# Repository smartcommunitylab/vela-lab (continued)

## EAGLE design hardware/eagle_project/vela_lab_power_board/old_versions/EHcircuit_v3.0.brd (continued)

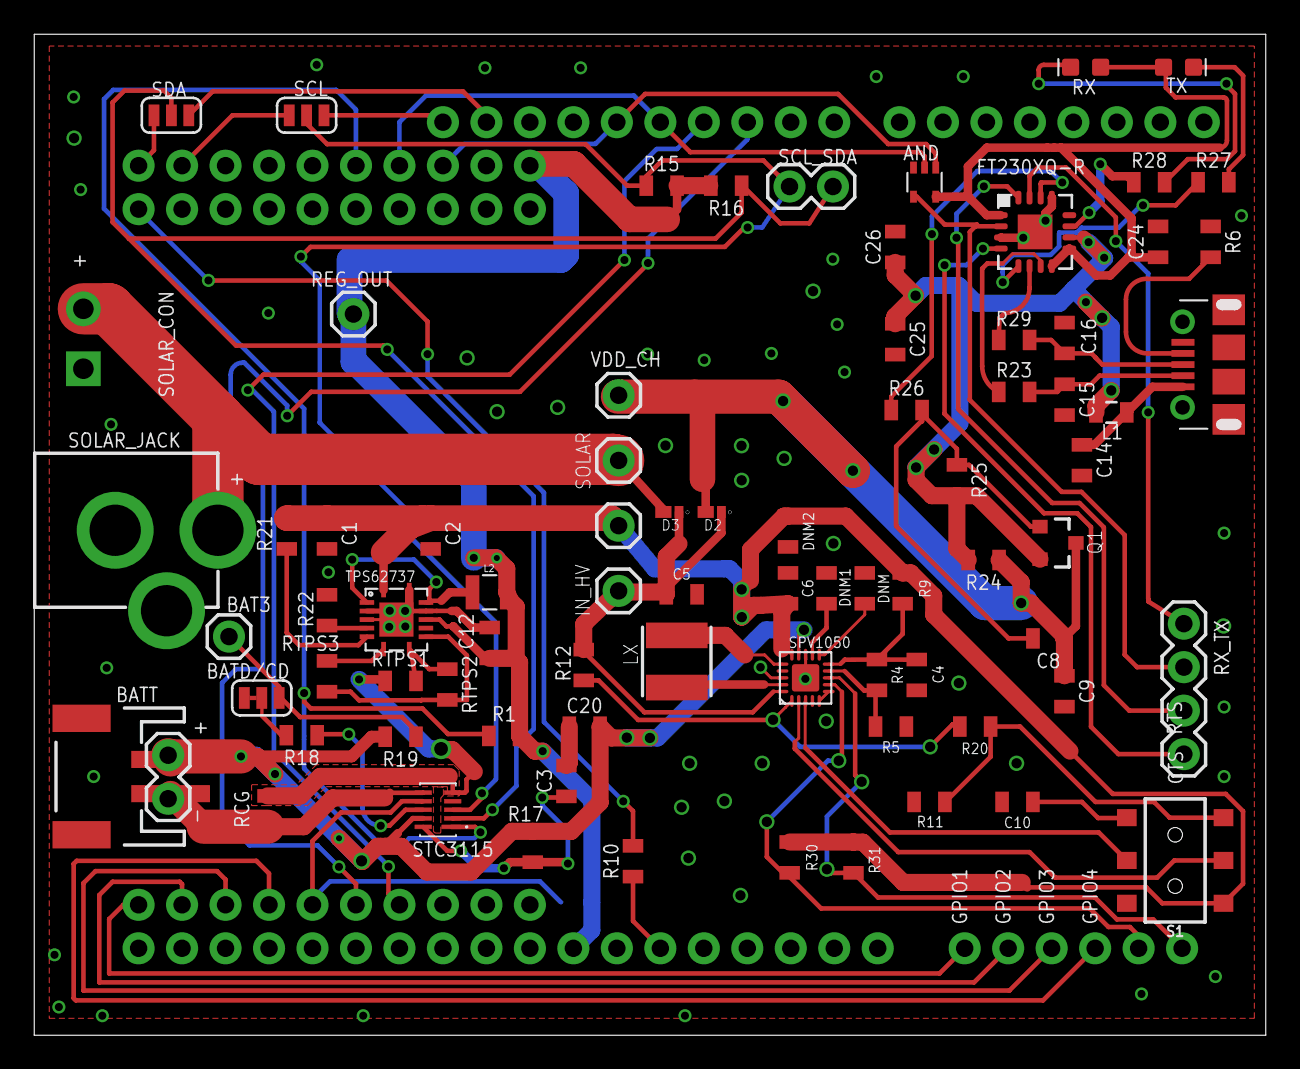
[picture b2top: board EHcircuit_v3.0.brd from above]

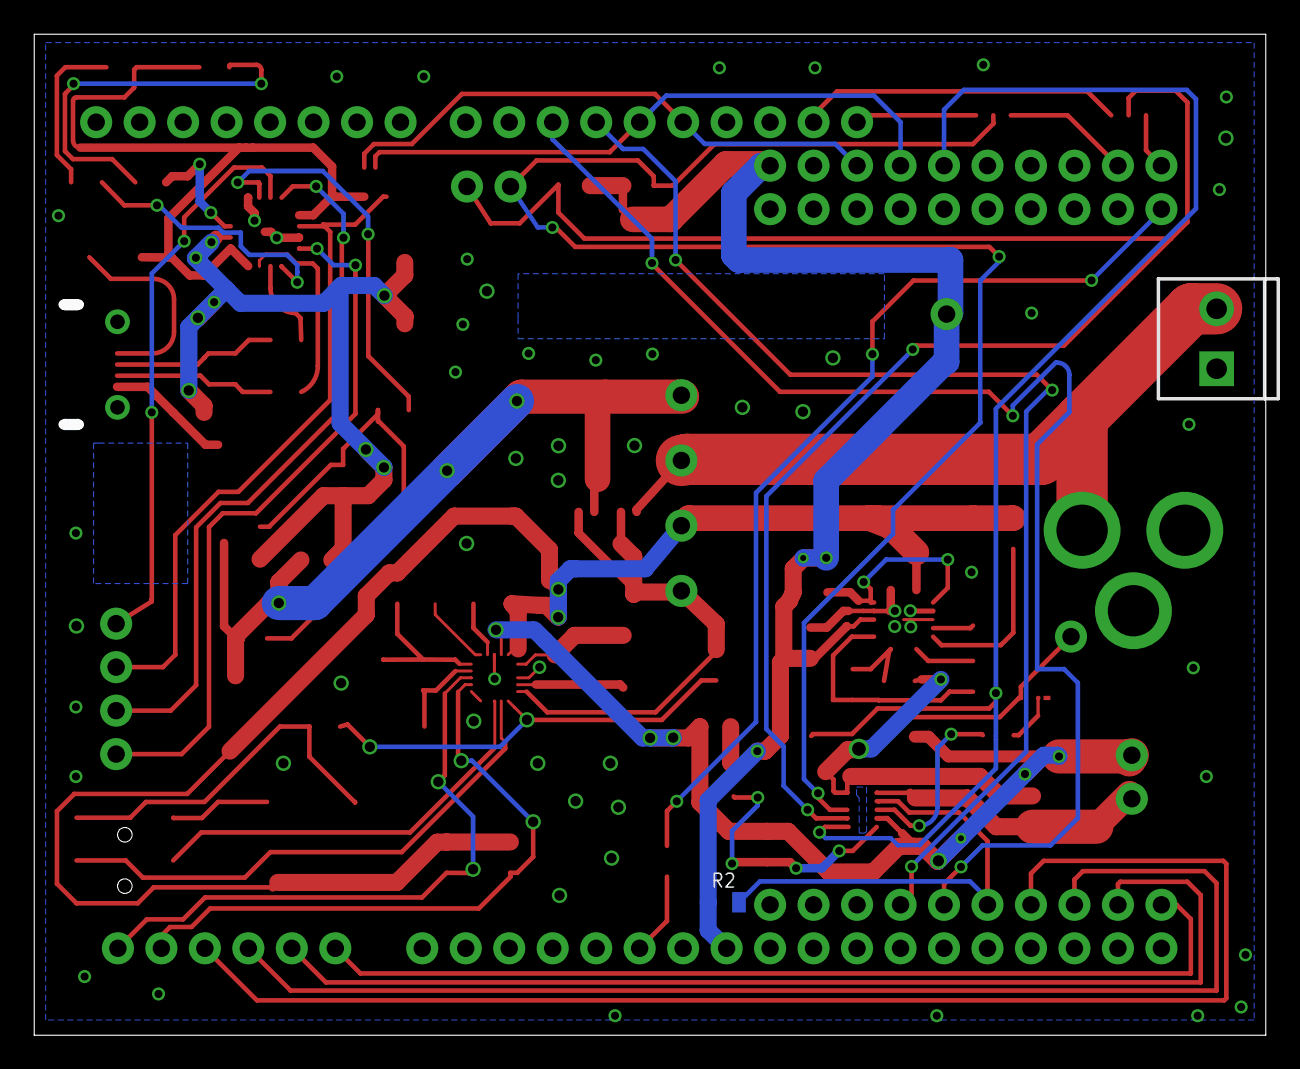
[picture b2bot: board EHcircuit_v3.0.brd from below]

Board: 2 copper layers, 71.9 x 58.5 mm, 82 parts (2 on the bottom side), 67 nets.

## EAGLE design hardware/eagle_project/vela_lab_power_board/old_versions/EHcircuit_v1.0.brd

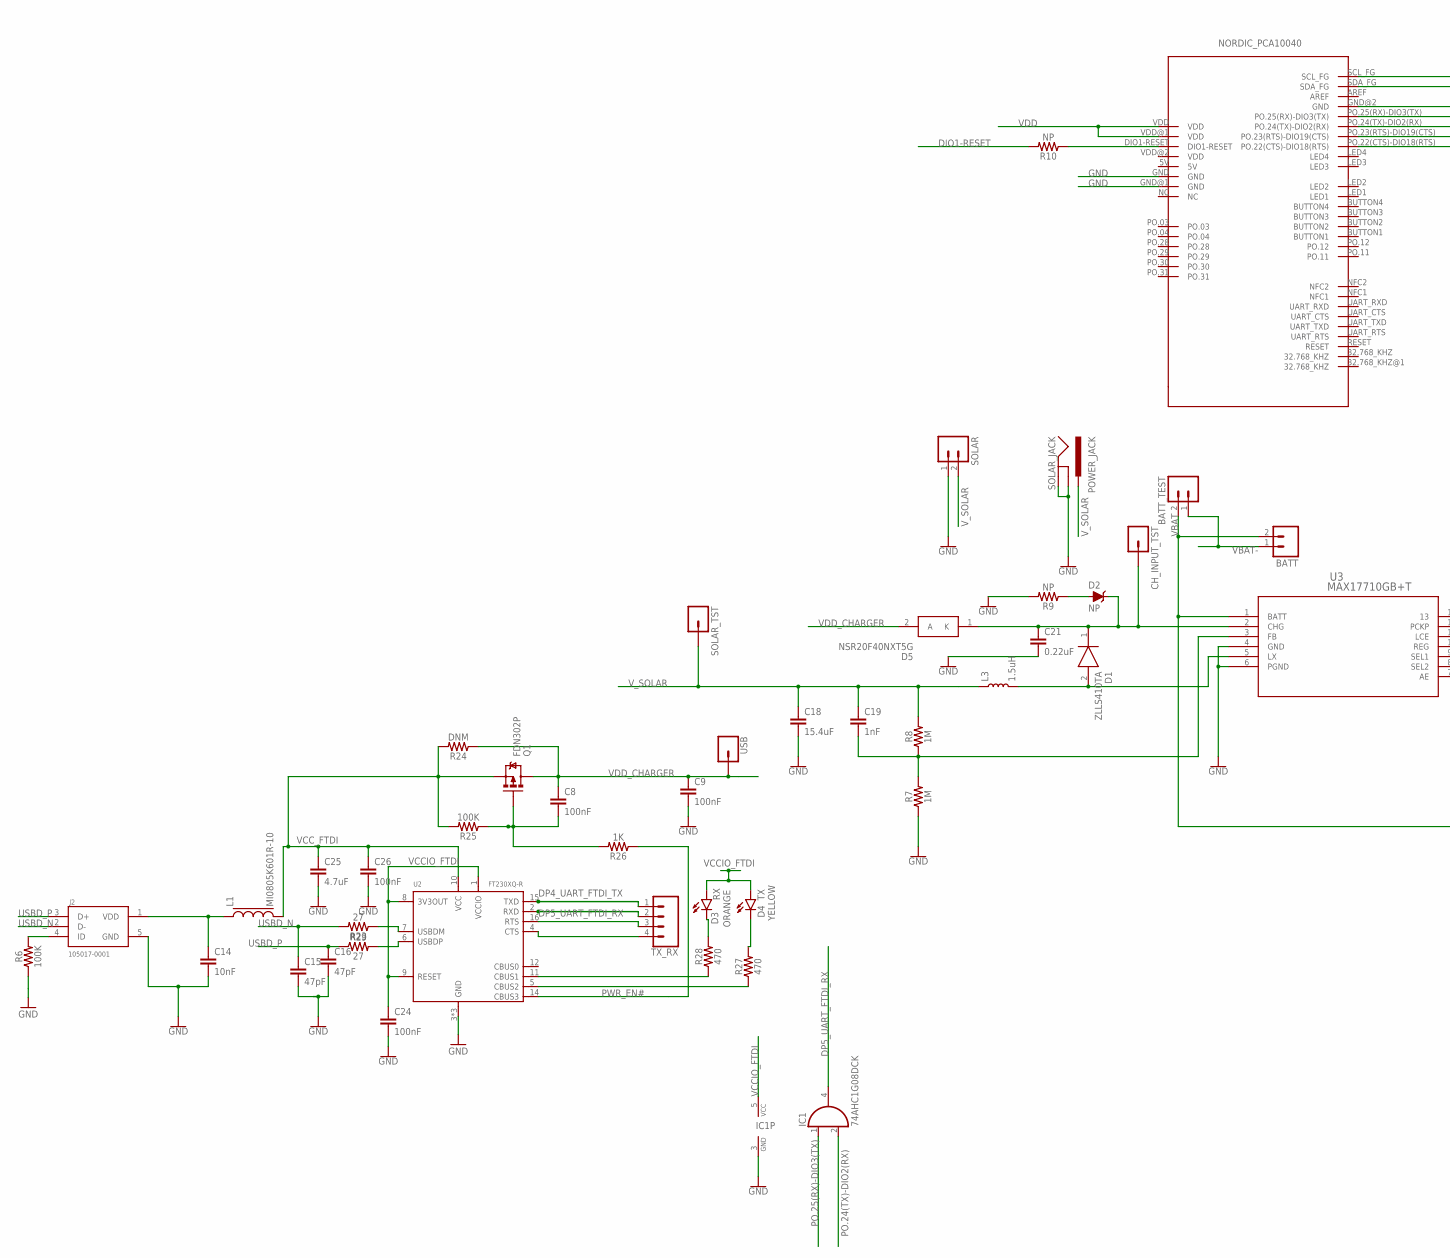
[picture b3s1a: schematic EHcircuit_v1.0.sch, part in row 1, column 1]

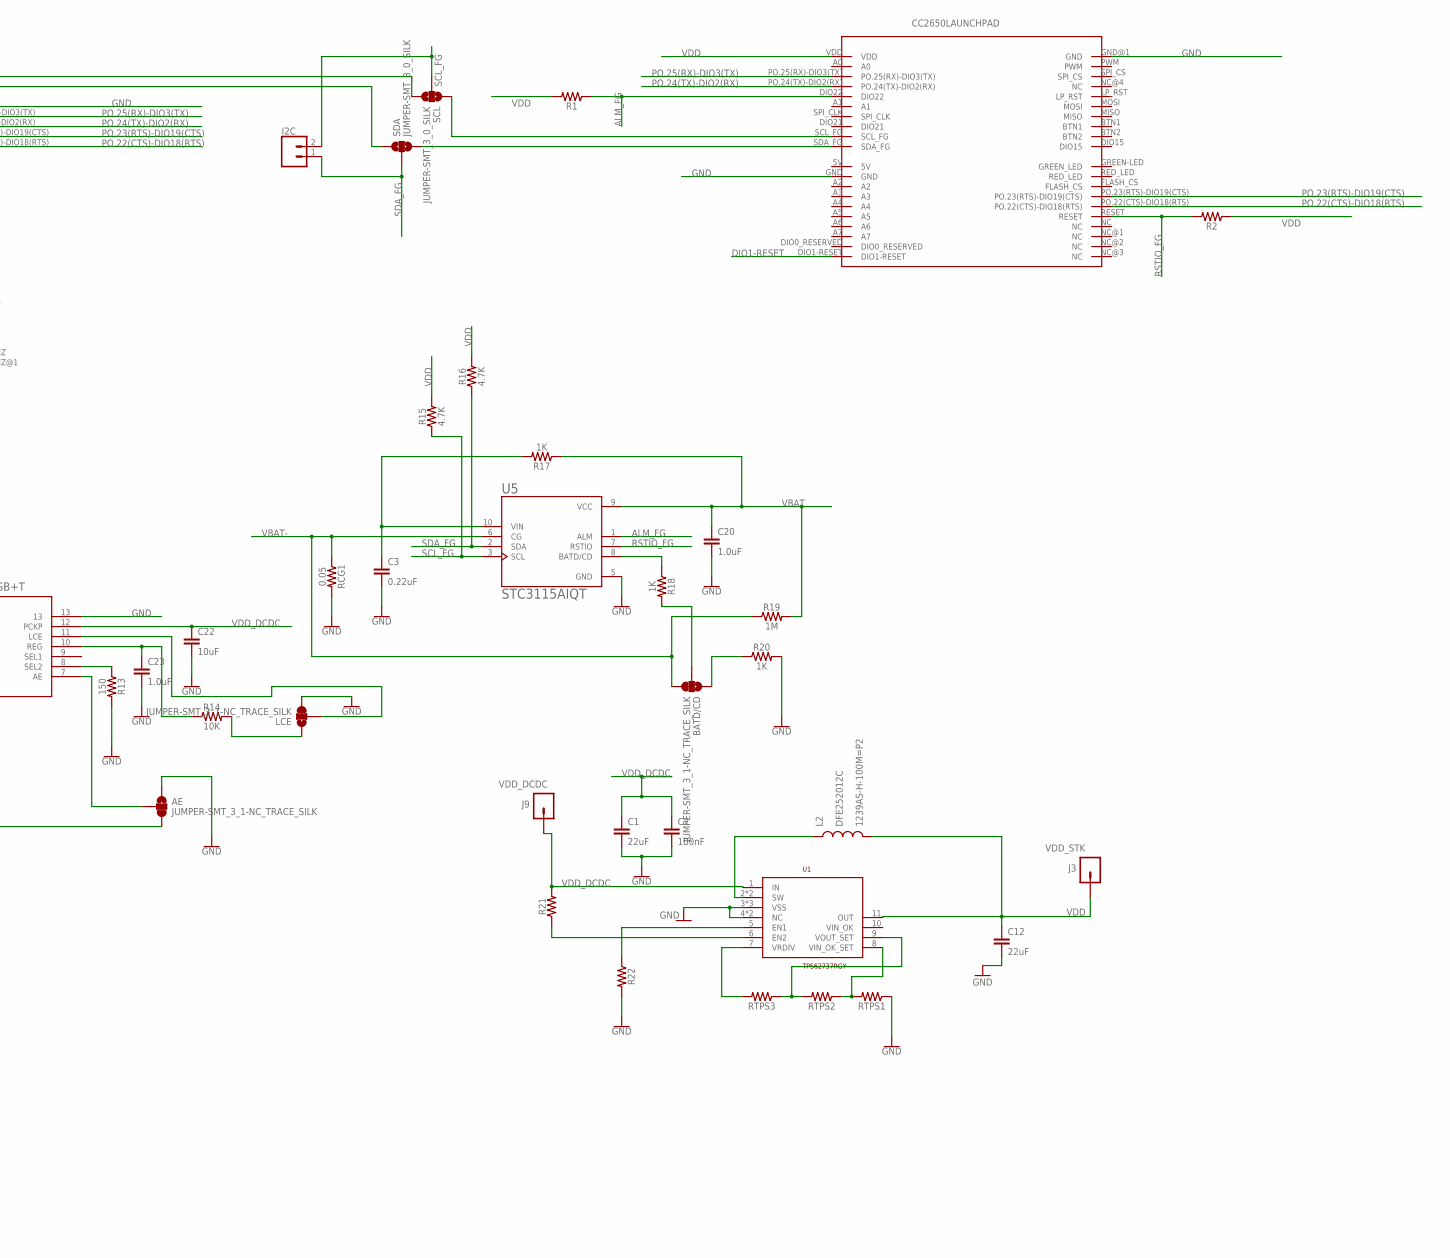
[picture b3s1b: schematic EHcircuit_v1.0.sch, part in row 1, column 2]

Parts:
AE: JUMPER-SMT_3_1-NC_TRACE_SILK; SMT-JUMPER_3_1-NC_TRACE_SILK
BATD/CD: JUMPER-SMT_3_1-NC_TRACE_SILK; SMT-JUMPER_3_1-NC_TRACE_SILK
BATT: M02-JST-2MM-SMT; JST-2-SMD@1
BATT_TEST: M02PTH; 1X02@1
C1, C12: 22uF; 0805
C2, C8, C9, C24, C26: 100nF; 0805
C3, C21: 0.22uF; 0805
C14: 10nF; 0805
C15, C16: 47pF; 0805
C18: 15.4uF; 0805
C19: 1nF; 0805
C20, C23: 1.0uF; 0805
C22: 10uF; 0805
C25: 4.7uF; 0805
CH_INPUT_TST: M01PTH; 1X01@1
D1: ZLLS410TA; SOD2513X120N
D2: NP; SOD-323@1
D3: ORANGE; LED-0603
D4: YELLOW; LED-0603
D5: NSR20F40NXT5G; DSN2_1
I2C: CONN_02; 1X02
IC1: 74AHC1G08DCK; SC70-5
J2: 105017-0001; MOLEX_105017-0001
J3, J9: M01PTH; 1X01@1
L1: MI0805K601R-10; 0805
L2: 1239AS-H-100M=P2; DFE252012C
L3: 1.5uH; XFL4020
LCE: JUMPER-SMT_3_1-NC_TRACE_SILK; SMT-JUMPER_3_1-NC_TRACE_SILK
Q1: FDN302P; SOT23-3
R1, R2, R21, R22: 0.3OHM-0805-1/8W-1%; 0805
R6, R25: 100K; 0805
R7, R8, R19: 1M; 0805
R9, R10: NP; 0805
R13: 150; 0805
R14: 10K; 0805
R15, R16: 4.7K; 0805
R17, R18, R20, R26: 1K; 0805
R23, R29: 27; 0805
R24: DNM; 0805
R27, R28: 470; 0805
RB2: CC2650LAUNCHPAD; SEPS_RB
RCG1: 0.05; 0805
RTPS1, RTPS2, RTPS3: 0.3OHM-0805-1/8W-1%; 0805
SCL: JUMPER-SMT_3_0_SILK; SMT-JUMPER_3_0_NC_TRACE_SILK
SDA: JUMPER-SMT_3_0_SILK; SMT-JUMPER_3_0_NC_TRACE_SILK
SOLAR: M023.5MM; SCREWTERMINAL-3.5MM-2@1
SOLAR_JACK: POWER_JACK; POWER_JACK_PTH
SOLAR_TST: M01PTH; 1X01@1
TX_RX: CONN_04; 1X04
U1: TPS62737RGY; QFN14
U2: FT230XQ-R; QFN16
U3: MAX17710GB+T; 21-0451C
U5: STC3115AIQT; SON50P200X300X60-10
U$1: PCA10040NORDIC; SEPS_BB
USB: CONN_01; 1X01

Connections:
ALM_FG: R1.1, RB2.DIO22, U5.1 (ALM)
DIO1-RESET: R10.2, RB2.DIO1-RESET
DP4_UART_FTDI_TX: TX_RX.1, U2.15 (TXD)
DP5_UART_FTDI_RX: IC1.4 (O), TX_RX.2, U2.2 (RXD)
GND: AE.1, C1.2, C2.2, C3.2, C9.2, C12.2, C14.2, C15.2, C16.2, C18.2, C20.2, C21.2, C22.2, C23.2, C24.2, C25.2, C26.2, IC1.3 (GND), J2.5 (GND), LCE.3, R6.1, R7.1, R9.2, R13.2, R20.2, R22.2, RB2.GND, RB2.GND@1 (GND), RCG1.2, RTPS1.1, SOLAR.1, SOLAR_JACK.GND, SOLAR_JACK.GNDBREAK, U1.3 (VSS), U1.4 (NC), U1.12 (VSS), U1.14 (NC), U1.TH_PAD (VSS), U2.3 (GND), U2.13 (GND), U2.17 (GND), U3.4 (GND), U3.6 (PGND), U3.13, U5.5 (GND), U$1.GND, U$1.GND@1 (GND), U$1.GND@2 (GND)
unnamed: R28.1, U2.11 (CBUS1)
unnamed: C14.1, J2.1 (VDD), L1.1
unnamed: C8.2, Q1.1 (G), R25.1, R26.2
unnamed: RTPS1.2, RTPS2.1, U1.8 (VIN_OK_SET)
unnamed: R18.1, U5.8 (BATD/CD)
unnamed: R22.1, U1.5 (EN1)
unnamed: D1.2 (A), L3.P$2 (2), U3.5 (LX)
unnamed: D2.A, R9.1
unnamed: C19.2, R7.2, R8.1, U3.3 (FB)
unnamed: R21.1, U1.6 (EN2)
unnamed: L2.P$1 (1), U1.2 (SW), U1.13 (SW)
unnamed: RB2.SCL_FG, SCL.1
unnamed: C23.1, R14.1, U3.10 (REG)
unnamed: R27.1, U2.5 (CBUS2)
unnamed: LCE.2, U3.11 (LCE)
unnamed: R13.1, U3.8 (SEL2)
unnamed: LCE.1, R14.2
unnamed: J2.4 (ID), R6.2
unnamed: AE.2, U3.7 (AE)
unnamed: D3.C, R28.2
unnamed: R10.1, U$1.DIO1-RESET
unnamed: RTPS3.2, U1.7 (VRDIV)
unnamed: RB2.SDA_FG, SDA.3
unnamed: D4.C, R27.2
unnamed: BATD/CD.2, R18.2
unnamed: RTPS2.2, RTPS3.1, U1.9 (VOUT_SET)
unnamed: SDA.1, U$1.SDA_FG
unnamed: SCL.3, U$1.SCL_FG
unnamed: BATD/CD.1, R20.1
unnamed: C21.1, CH_INPUT_TST.1, D1.1 (K), D2.C, D5.1 (K), U3.2 (CHG)
unnamed: R23.1, U2.7 (USBDM)
unnamed: R29.2, U2.6 (USBDP)
unnamed: TX_RX.3, U2.16 (RTS)
unnamed: C3.1, R17.2, U5.10 (VIN)
unnamed: TX_RX.4, U2.4 (CTS)
PO.22(CTS)-DIO18(RTS): RB2.PO.22(CTS)-DIO18(RT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, U$1.PO.22(CTS)-DIO18(RT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
PO.23(RTS)-DIO19(CTS): RB2.PO.23(RTS)-DIO19(CT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, U$1.PO.23(RTS)-DIO19(CT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
PO.24(TX)-DIO2(RX): IC1.2 (I1), RB2.PO.24(TX)-DIO2(RX), U$1.PO.24(TX)-DIO2(RX)
PO.25(RX)-DIO3(TX): IC1.1 (I0), RB2.PO.25(RX)-DIO3(TX), U$1.PO.25(RX)-DIO3(TX)
PWR_EN#: R26.1, U2.14 (CBUS3)
RSTIO_FG: R2.2, RB2.RESET, U5.7 (RSTIO)
SCL_FG: I2C.2, R15.1, SCL.2, U5.3 (SCL)
SDA_FG: I2C.1, R16.1, SDA.2, U5.2 (SDA)
USBD_N: C15.1, J2.2 (D-), R23.2
USBD_P: C16.1, J2.3 (D+), R29.1
VBAT: AE.3, BATT.2 (1), BATT_TEST.2, C20.1, R17.1, R19.2, U3.1 (BATT), U5.9 (VCC)
VBAT-: BATD/CD.3, BATT.1 (2), BATT_TEST.1, R19.1, RCG1.1, U5.6 (CG)
VCCIO_FTDI: C24.1, D3.A, D4.A, IC1.5 (VCC), U2.1 (VCCIO), U2.8 (3V3OUT), U2.9 (RESET)
VCC_FTDI: C25.1, C26.1, L1.2, Q1.2 (S), R24.2, R25.2, U2.10 (VCC)
VDD: C12.1, J3.1, L2.P$2 (2), R1.2, R2.1, R15.2, R16.2, RB2.VDD, U1.11 (OUT), U$1.VDD, U$1.VDD@1 (VDD)
VDD_CHARGER: C8.1, C9.1, D5.2 (A), Q1.3 (D), R24.1, USB.1
VDD_DCDC: C1.1, C2.1, C22.1, J9.1, R21.2, U1.1 (IN), U3.12 (PCKP)
V_SOLAR: C18.1, C19.1, L3.P$1 (1), R8.2, SOLAR.2, SOLAR_JACK.PWR, SOLAR_TST.1

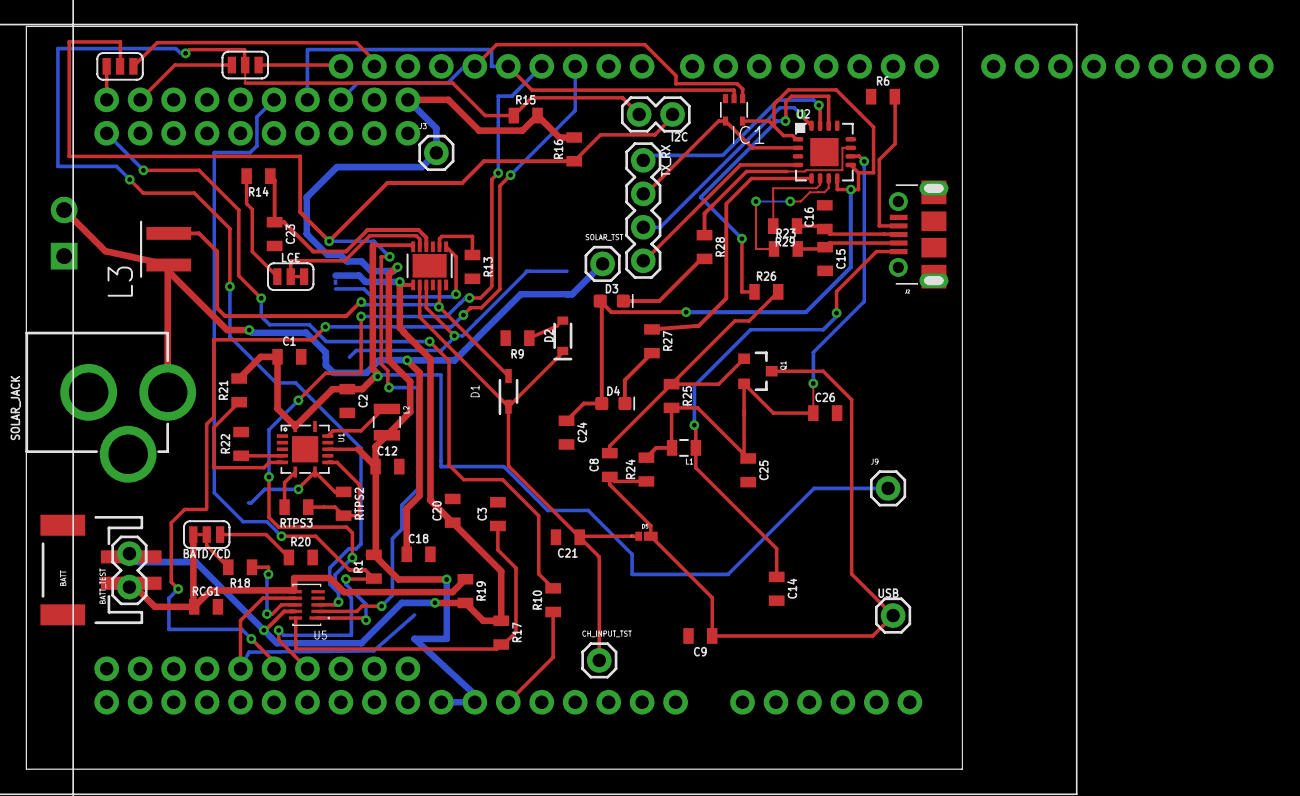
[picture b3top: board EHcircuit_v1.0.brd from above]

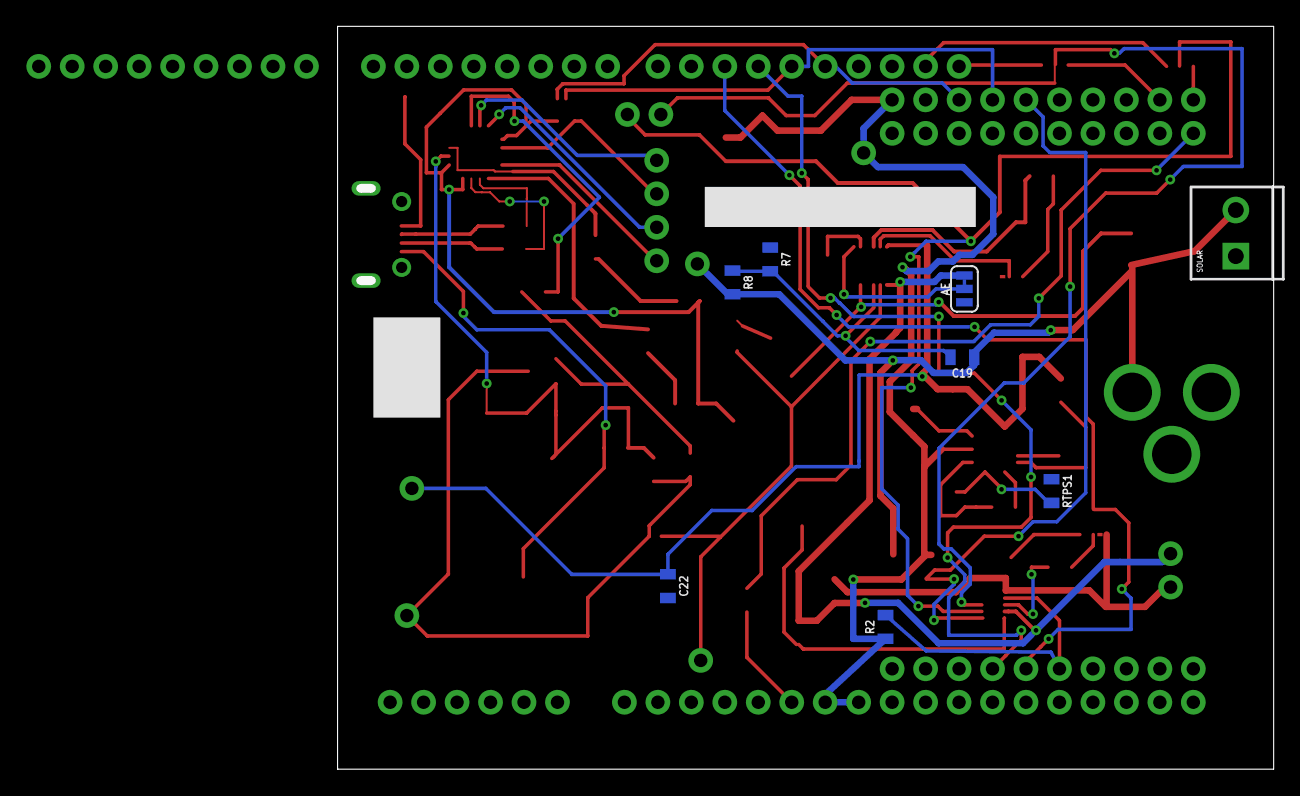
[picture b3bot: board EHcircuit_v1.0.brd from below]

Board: 2 copper layers, 71.0 x 56.4 mm, 79 parts (8 on the bottom side), 58 nets.

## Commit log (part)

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2017-11-15 First commit
    First version of the code (anyway it compiles and works).
    This commit is only for backup purposes
2017-11-17 Various improvements on UART communication and BLE scanning
    - uart ack change to application ack
    - add uart_resp_bt_neigh_rep_end type to indicate the report is over
    - ack error now have one argument with some data regarding the ack
    - added contraints.h which contains various constants used by the projects
    - added filter for BLE beacons (filters CLIMBC nodes and eddystone with the correct namespace)
    - Makefile clean
2017-11-17 Changing report
    - now the "seen_since" field of the report is in second (16 bits), no more in millis
    - the report includes also the beacon_msg_count
2017-11-21 Blink led on nrf52dk and code version on both boards
    - an uart ack error is signaled with a blink of led4 in the nrf52dk
    - the code version string is added as payload of the uart_ready messagges. The build number is automatically increased by the build_script.sh. Thi
2017-11-21 Minor changes on app_timer (nrf52dk)
2017-11-21 Use struct in place of ptr+size
    moving data_t into uart_util.h so that now it is shared
2017-11-21 integration code --- currently not working
2017-11-21 Moving the uart flow control enable outside contiki sources
    By default contiki do not enable flow control on the uart but we need it.
    Now the enable is done in uart_util.c when the initialization routine is called.
2017-11-22 Updated to match the new structure of the test directories
2017-11-22 bringing makefile in line with new unit test structure for uart
2017-11-22 moving the shared struct definition of the buffer to common/inc/constraints.h
2017-11-22 Remove test-uart.c
    the file content has been moved to vela_uart.c
2017-11-22 working version of the dummy uart with the real RPL sender and receiver.
2017-11-22 fixing repository to add missing files for test sender
2017-11-22 Bug fix
    There was a logic error when the report was splitted in multiple uart packets.
2017-11-22 Bug fix for reports on splitted uart packets
2017-11-22 Adding simple readme to "integrate_sender_uart"
2017-11-23 Bojan: git setup test
2017-11-23 fixing debug to off
2017-11-23 Bojan: excluded aux files for linux folder
2017-11-23 Version 0.1
    Not stable but seems to work
2017-11-28 BM: added gateway subdir and code
2017-11-28 BM: doc update
2017-11-28 decreasing uart baudrate
    working at 1M give errors, then switch to 115200
2017-11-29 BM: corrected typo in /gateway/dev/serial_test/
2017-11-30 Reduce BT scan duty cycle
2017-11-30 BM: serial testing
2017-11-30 Minor optimization/fix
2017-11-30 BM: serial for real packets (not decoded)
2017-12-01 BM: added serial test log and gitignore
2017-12-01 BM: serial test log update
2017-12-04 uart_util optimization/fix
    This fix lightly reinforce the uart communication
2017-12-04 channel check rate change
2017-12-05 uart tx_error led fix
    the tx_error led weren't reset properly
2017-12-05 BM: gateway integration dev
2017-12-06 remove printf during
2017-12-07 BM: packet read lenght check
2017-12-12 BM: added app log
2017-12-13 BM: packet reception testing
2017-12-15 Reorganization of defines in the header files
    The rpl packet size has been increased from 10 to 15 contacts
2017-12-15 BM: added matlab folder and scripts
2017-12-20 BM: added demo script
2018-01-25 Comments change
    Just adding comments and removing some useless stuf
2018-10-02 New design added
2018-10-05 Small fixes pcb design
2018-10-05 First check. Few things to modify:
    - rearrange kelvin connections on sensing resistor (and routing around the fuel gauge)
    - add LED on CBUS1 and CBUS2 of the FTDI chip (see powerDevPack project), or remove the CBUS1 and CBUS2 connections
    - edit the JST connector footprint and increase holes size (see J5 footprint as reference)
2018-10-08 Changed drill holes in JST connectors
2018-10-08 Updated .gitignore file
2018-10-08 Changed sense resistor
2018-11-12 commiting the PCB printed ad eurocircuit (very first version)
2018-11-26 Add UART interupt priority on VELA NODES
2018-11-26 Fix CCS project
2018-11-26 add workaround the TX/RX swap in the solar panel board
2018-11-26 minor fix to a makefile
2018-11-27 Small change in the uart_util.c
    There was a risk of entering infinite loop if the status = error
2018-11-28 putchar fix
2018-11-28 All makefile are now similar
2018-11-29 PCB project update
    - arduino header fix
    - text fix
    - library refactor (now all the capacitor use the same component as well as resistors)
2018-12-05 Adding MAX17260 temperature reading
2018-12-06 Updated network messages types
2018-12-06 getting rid of the fsm. Now vela_uart uses procedures to execute queue of commands
2018-12-07 add uart_util_is_waiting_ack to uart_util
2018-12-07 Code used for test with fuel gauge and gateway commands
2018-12-12 Sequential procedures module
    - now to communicate over the uart both boards use sequential_procedure module
    - added log over rtt on the nordic
    - added verbosity on both boards
2018-12-12 Stable version?
2018-12-13 gitignore
2018-12-13 trickle fix (multihop was not working)
2018-12-14 commented part forgotten
2018-12-19 Changed raw data logging formatting
2018-12-19 Adding delay to ack.
    It seemed that the TI sent the uart ack to fast and the nordic wasn't able to handle it
2018-12-19 message number fix
2018-12-20 Changed raw data logging for bluetooth reports
2018-12-20 Clean up gateway code
2018-12-21 Add a delay on ack also on nordic and on sequential procedures
2019-01-02 increasing ser usability.
    Now, on the gateway script, if the serial line has an exception the script keep checking every 5s and if it returns available the script restart working
2019-01-03 minor change: activating bluetooth scheduling (30 min on/30 min off)
2019-01-04 minor PRINTF change
2019-01-04 fix on report timeout.
    Now it properly stores the last value and use it till a new timeout is received from the mesh network
2019-01-04 Minor parameters change
2019-01-07 Fixed contact data plotter
2019-01-10 Increased max packet size
2019-01-14 Updated network_commands document
2019-01-15 Restructuring and changing documentation
2019-01-15 Edited README.md
2019-01-28 minor bug (if nordic was reset and the report was enabled a reset was triggered)
2019-01-29 regardless where the script is launched, logs are always in the same position of the script
2019-01-29 Merge branch 'master' of https://github.com/smartcommunitylab/vela-lab
    # Please enter a commit message to explain why this merge is necessary,
    # especially if it merges an updated upstream into a topic branch.
    #
    # Lines starting with '#' will be ignored, and an empty message aborts
    # the commit.
2019-01-29 remove self reset with NORDIC_WATCHDOG_ENABLED
2019-01-30 allow events on ti even if ready message from nordic isn't received
    this otherwise the nordic cannot be recovered after a bad boot
2019-01-31 redesign of the terminal interface
2019-02-01 minor graphical stuff on python script
2019-02-05 bug fix
2019-02-18 add 'forced' option to trickle messages
2019-02-18 Better handling of unknwown uart part
2019-02-19 a random delay is added to the handling of all the trickle packets. This to avoid collisions
2019-02-21 Some graphical fix and improvement and general log revision
2019-03-06 adding command line argument to set the port
2019-03-13 adding a kind of lock to avoid command handling during the transmission of the BLE report from the nordic to the TI, also a better handling of uart_util_ack_error
2019-03-13 minor makefile change
2019-05-15 Code cleanup - especially for send messages - ALM increased network message size to 22 entries - ALM
2019-05-15 gitignore + build.sh
2019-07-04 adding basic sender that works in cooja
2019-07-04 fixed type-o
2019-08-08 first commit with OTA. There are still things to fix, with all the code, the OTA cannot be verified because of memory overflow and the node reboots.
2019-08-12 fix in doc
2019-08-12 more reliable ota
2019-08-16 better ota
    If the node doesn't have enough free ram to store the CRC result in the ext-flash, it will be the bootloader to do it on the next reboot.
2019-08-20 bug fix in OTA that locked the bootloader in an infinite loop in case of crc error
2019-08-22 added the payload checksum in the gateway to sink communication
2019-08-26 Checksum fix on sink
2019-08-30 gitignore and some experiment log
2019-09-02 Various proximity detection algorithm improvements
2019-09-03 stronger algorithm and octave for raspberry (installed with flatpak)
2019-10-08 code clean e better gui (with fw info embedded)
2019-10-09 some cleaning and network status generation for mqtt push
2019-10-11 stability updates
2019-10-11 Main readme and other doc update
2019-10-11 remove bin
2019-10-14 Readme
2019-10-14 VSCode+GDB+openOCD working
    Some configuration such as those involving the bootloader are still not working.
    Removed all the references to eclipse and derivatives
2019-10-17 add mqtt connection to thingsboard
2019-10-17 change the format of events generated by the octave script
    Now the format is ready to be pushed on a gateway device of thingsboard
2019-10-18 Environment fix
    - files are no more copied to integrate_sender_uart
    - files such as vela_uart.c/.h vela_sender.c/h and others are now packed as contiki modules
    - some contiki test projects (no more used) have been moved to old/ directory
    - improved clean.sh
    - improved build scripts
    - added the VSCode tasks to compile for OTA download
2019-10-24 mqtt connection check + other minor changes
2019-10-24 sink baudrate to 1M (second)
2019-10-29 relative path for startup script
2019-10-29 re-enable logs, without logs the sink reboots during ota
2019-10-30 minor things
2019-11-20 change in the message format transmitted to thingsboard
2019-11-20 add the vscode launch configuration for the gateway
2019-11-22 get beacon improvement
    - now it loops over all the nodes (node list is hardcoded)
2019-12-04 moving contiki to gitlab and embedding NRF SDK in the repo through a submodule
    Moreover few README change
2019-12-04 readme update
2019-12-04 readme format
2019-12-04 readme update n
2019-12-04 change to README-BUILDING
2019-12-04 typos in readmes
2019-12-18 my last commit with residual changes
    - bug fix on main.py
    - workspace with relative paths
    - bug fix in backend scripts
    - minor improvements here and there
2020-11-12 added version file to gitignore
2020-11-12 added vela_node_with_bootloader to gitignore
2020-11-16 shifted main inside if __main__ and added another token
2020-11-16 starting to collect packages in requirements
2020-11-18 porting the variables to different files
2020-11-19 unique file containing the parameters
2020-11-20 modification to the proximity detection trhough octave
2020-11-20 added comment
2020-11-20 moved the on_events because not related with the class itself
2020-11-25 log folder issue
2020-11-27 moved bluetooth parameters, but the command 5 still doesn't work
2020-12-01 added threading and firmware variables, some counter for callback debugging
2020-12-10 bluetooth scheduler, still too many beacon generates problems
2020-12-14 decode payload modified input parameters
2020-12-15 added possibility to disable bluetooth scheduler and proximity detection script
2021-01-19 added file for beacon processing
2021-02-22 changed sleep function, removed useless initialization in processo uart rx function
2021-02-22 modification about TOF and GATT
2021-03-29 backup for app_uart library, even if not working in vela-system
2021-04-20 nb_report_util added
2021-04-23 included Makefile.posix in gitignore
2021-04-23 assume unchanged to makefile.posix
2021-04-23 DELETED BINARIES
2021-04-23 fixed gitignore
2021-04-28 tidy up folders structure
2021-05-04 started vela_spi.c and .h
2021-08-24 added modified contiki_ng
2021-08-25 removed submodule
2021-08-25 removed contiki backup
2021-09-09 Add cc1310 target
